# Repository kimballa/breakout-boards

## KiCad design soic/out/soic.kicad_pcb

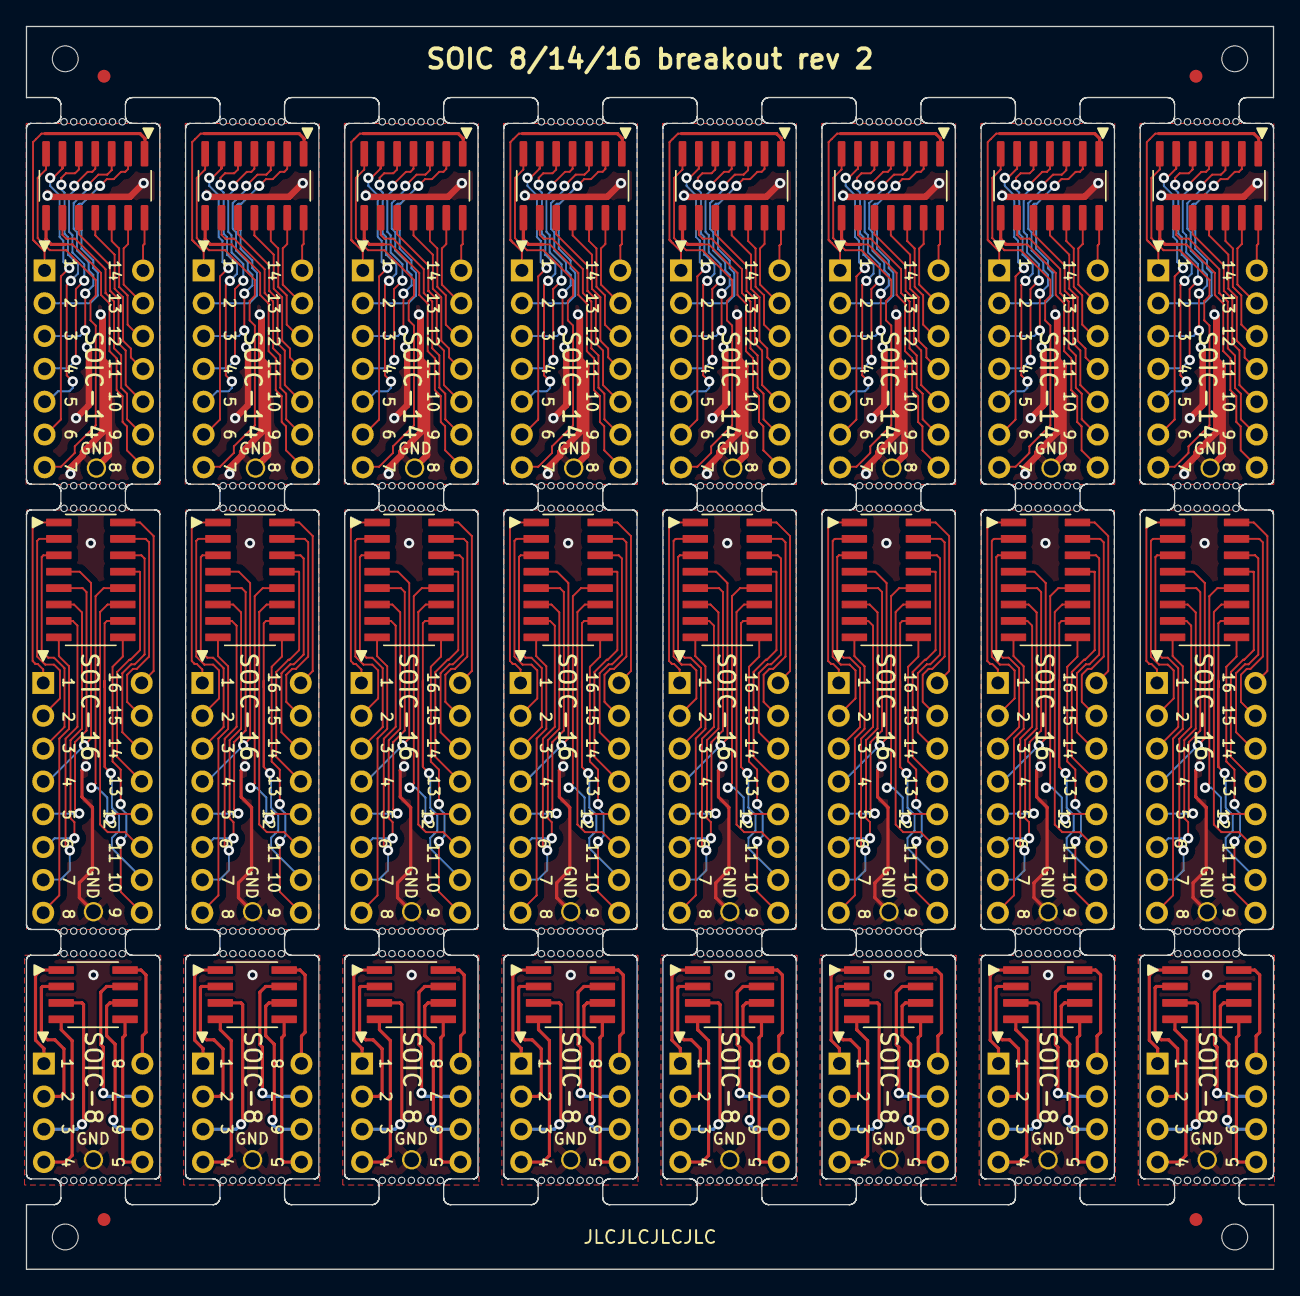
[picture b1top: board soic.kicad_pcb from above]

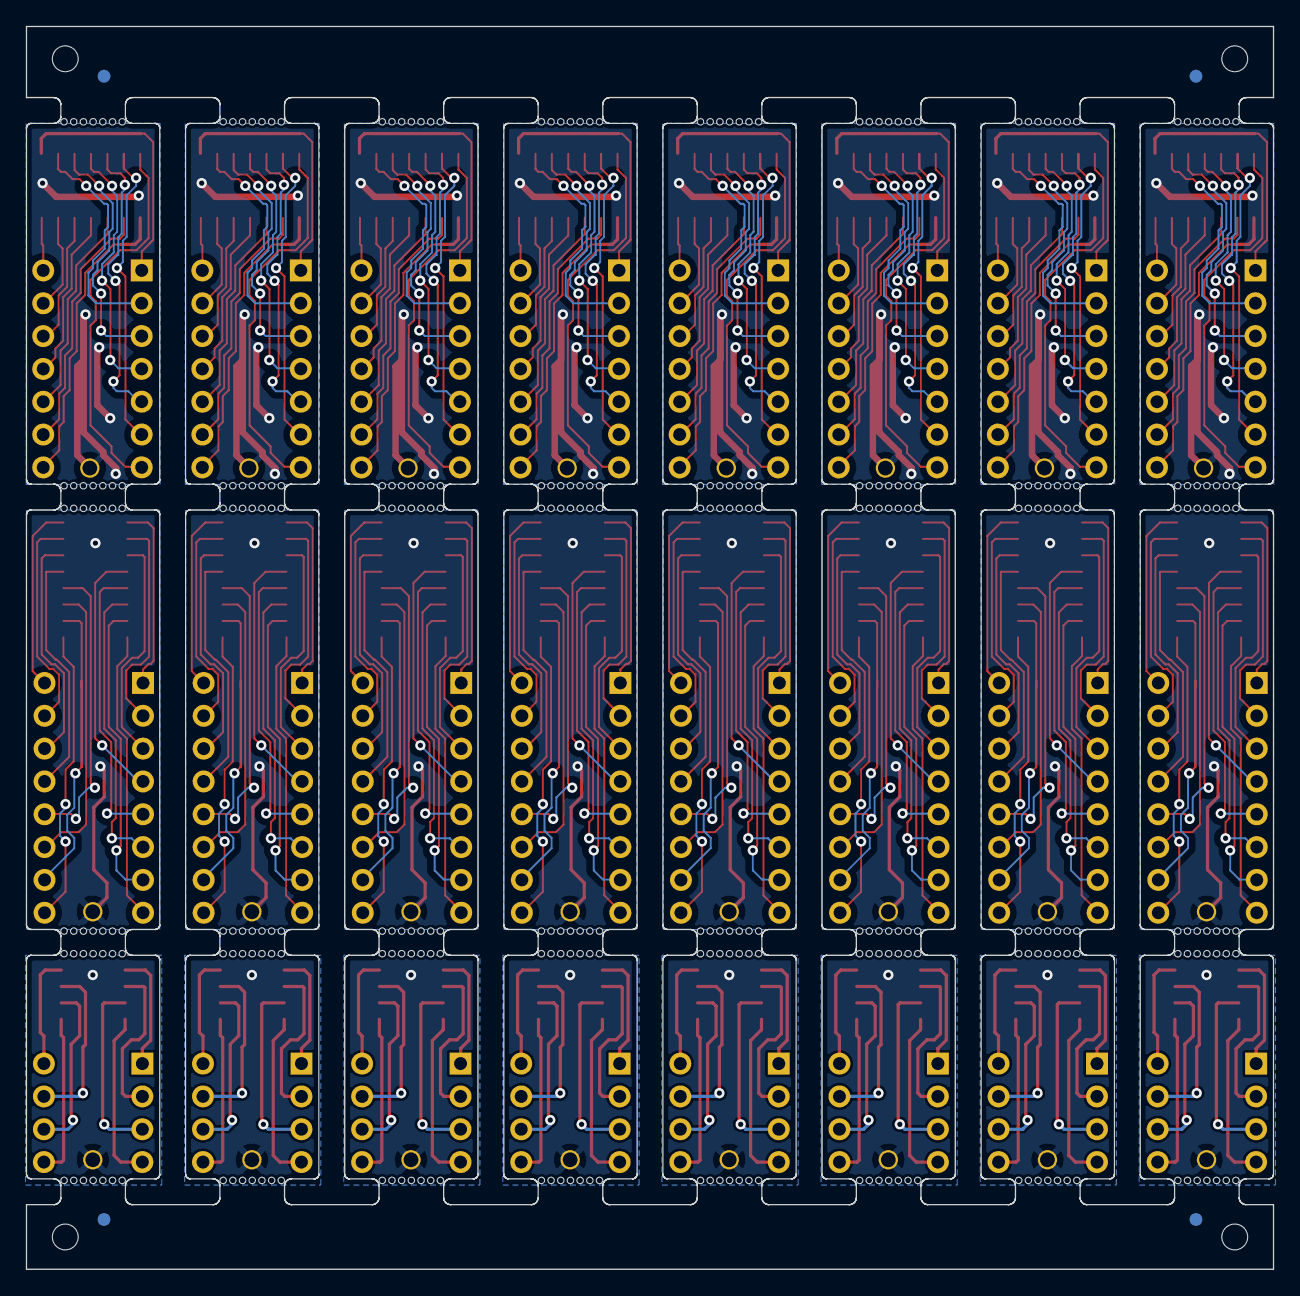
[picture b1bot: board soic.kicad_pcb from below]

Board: 2 copper layers, 96.5 x 96.2 mm, 444 parts (4 on the bottom side), 304 nets.

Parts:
J1, J1#2, J1#3, J1#4, J1#5, J1#6, J1#7, J1#8, J2, J2#2, J2#3, J2#4, J2#5, J2#6, J2#7, J2#8: Conn_01x07; PinHeader_1x07_P2.54mm_Vertical
J3, J3#2, J3#3, J3#4, J3#5, J3#6, J3#7, J3#8, J6, J6#2, J6#3, J6#4, J6#5, J6#6, J6#7, J6#8, J7, J7#2, J7#3, J7#4, J7#5, J7#6, J7#7, J7#8: Conn_01x01; TP_HeaderPin_P2.54mm_round
J4, J4#2, J4#3, J4#4, J4#5, J4#6, J4#7, J4#8, J5, J5#2, J5#3, J5#4, J5#5, J5#6, J5#7, J5#8: Conn_01x08; PinHeader_1x08_P2.54mm_Vertical
J8, J8#2, J8#3, J8#4, J8#5, J8#6, J8#7, J8#8, J9, J9#2, J9#3, J9#4, J9#5, J9#6, J9#7, J9#8: Conn_01x04; PinHeader_1x04_P2.54mm_Vertical
KiKit_FID_B_1, KiKit_FID_B_2, KiKit_FID_B_3, KiKit_FID_B_4: Fiducial
KiKit_FID_T_1, KiKit_FID_T_2, KiKit_FID_T_3, KiKit_FID_T_4: Fiducial
KiKit_MB_1_4, KiKit_MB_1_5, KiKit_MB_1_6, KiKit_MB_1_7, KiKit_MB_1_8, KiKit_MB_1_9, KiKit_MB_1_10, KiKit_MB_2_4, KiKit_MB_2_5, KiKit_MB_2_6, KiKit_MB_2_7, KiKit_MB_2_8, KiKit_MB_2_9, KiKit_MB_2_10, KiKit_MB_3_4, KiKit_MB_3_5, KiKit_MB_3_6, KiKit_MB_3_7, KiKit_MB_3_8, KiKit_MB_3_9, KiKit_MB_3_10, KiKit_MB_4_4, KiKit_MB_4_5, KiKit_MB_4_6, KiKit_MB_4_7, KiKit_MB_4_8, KiKit_MB_4_9, KiKit_MB_4_10, KiKit_MB_5_4, KiKit_MB_5_5, KiKit_MB_5_6, KiKit_MB_5_7, KiKit_MB_5_8, KiKit_MB_5_9, KiKit_MB_5_10, KiKit_MB_6_4, KiKit_MB_6_5, KiKit_MB_6_6, KiKit_MB_6_7, KiKit_MB_6_8, KiKit_MB_6_9, KiKit_MB_6_10, KiKit_MB_7_4, KiKit_MB_7_5, KiKit_MB_7_6, KiKit_MB_7_7, KiKit_MB_7_8, KiKit_MB_7_9, KiKit_MB_7_10, KiKit_MB_8_4, KiKit_MB_8_5, KiKit_MB_8_6, KiKit_MB_8_7, KiKit_MB_8_8, KiKit_MB_8_9, KiKit_MB_8_10, KiKit_MB_9_4, KiKit_MB_9_5, KiKit_MB_9_6, KiKit_MB_9_7, KiKit_MB_9_8, KiKit_MB_9_9, KiKit_MB_9_10, KiKit_MB_10_4, KiKit_MB_10_5, KiKit_MB_10_6, KiKit_MB_10_7, KiKit_MB_10_8, KiKit_MB_10_9, KiKit_MB_10_10, KiKit_MB_11_4, KiKit_MB_11_5, KiKit_MB_11_6, KiKit_MB_11_7, KiKit_MB_11_8, KiKit_MB_11_9, KiKit_MB_11_10, KiKit_MB_12_4, KiKit_MB_12_5, KiKit_MB_12_6, KiKit_MB_12_7, KiKit_MB_12_8, KiKit_MB_12_9, KiKit_MB_12_10, KiKit_MB_13_4, KiKit_MB_13_5, KiKit_MB_13_6, KiKit_MB_13_7, KiKit_MB_13_8, KiKit_MB_13_9, KiKit_MB_13_10, KiKit_MB_14_4, KiKit_MB_14_5, KiKit_MB_14_6, KiKit_MB_14_7, KiKit_MB_14_8, KiKit_MB_14_9, KiKit_MB_14_10, KiKit_MB_15_4, KiKit_MB_15_5, KiKit_MB_15_6, KiKit_MB_15_7, KiKit_MB_15_8, KiKit_MB_15_9, KiKit_MB_15_10, KiKit_MB_16_4, KiKit_MB_16_5, KiKit_MB_16_6, KiKit_MB_16_7, KiKit_MB_16_8, KiKit_MB_16_9, KiKit_MB_16_10, KiKit_MB_17_4, KiKit_MB_17_5, KiKit_MB_17_6, KiKit_MB_17_7, KiKit_MB_17_8, KiKit_MB_17_9, KiKit_MB_17_10, KiKit_MB_18_4, KiKit_MB_18_5, KiKit_MB_18_6, KiKit_MB_18_7, KiKit_MB_18_8, KiKit_MB_18_9, KiKit_MB_18_10, KiKit_MB_19_4, KiKit_MB_19_5, KiKit_MB_19_6, KiKit_MB_19_7, KiKit_MB_19_8, KiKit_MB_19_9, KiKit_MB_19_10, KiKit_MB_20_4, KiKit_MB_20_5, KiKit_MB_20_6, KiKit_MB_20_7, KiKit_MB_20_8, KiKit_MB_20_9, KiKit_MB_20_10, KiKit_MB_21_4, KiKit_MB_21_5, KiKit_MB_21_6, KiKit_MB_21_7, KiKit_MB_21_8, KiKit_MB_21_9, KiKit_MB_21_10, KiKit_MB_22_4, KiKit_MB_22_5, KiKit_MB_22_6, KiKit_MB_22_7, KiKit_MB_22_8, KiKit_MB_22_9, KiKit_MB_22_10, KiKit_MB_23_4, KiKit_MB_23_5, KiKit_MB_23_6, KiKit_MB_23_7, KiKit_MB_23_8, KiKit_MB_23_9, KiKit_MB_23_10, KiKit_MB_24_4, KiKit_MB_24_5, KiKit_MB_24_6, KiKit_MB_24_7, KiKit_MB_24_8, KiKit_MB_24_9, KiKit_MB_24_10, KiKit_MB_25_4, KiKit_MB_25_5, KiKit_MB_25_6, KiKit_MB_25_7, KiKit_MB_25_8, KiKit_MB_25_9, KiKit_MB_25_10, KiKit_MB_26_4, KiKit_MB_26_5, KiKit_MB_26_6, KiKit_MB_26_7, KiKit_MB_26_8, KiKit_MB_26_9, KiKit_MB_26_10, KiKit_MB_27_4, KiKit_MB_27_5, KiKit_MB_27_6, KiKit_MB_27_7, KiKit_MB_27_8, KiKit_MB_27_9, KiKit_MB_27_10, KiKit_MB_28_4, KiKit_MB_28_5, KiKit_MB_28_6, KiKit_MB_28_7, KiKit_MB_28_8, KiKit_MB_28_9, KiKit_MB_28_10, KiKit_MB_29_4, KiKit_MB_29_5, KiKit_MB_29_6, KiKit_MB_29_7, KiKit_MB_29_8, KiKit_MB_29_9, KiKit_MB_29_10, KiKit_MB_30_4, KiKit_MB_30_5, KiKit_MB_30_6, KiKit_MB_30_7, KiKit_MB_30_8, KiKit_MB_30_9, KiKit_MB_30_10, KiKit_MB_31_4, KiKit_MB_31_5, KiKit_MB_31_6, KiKit_MB_31_7, KiKit_MB_31_8, KiKit_MB_31_9, KiKit_MB_31_10, KiKit_MB_32_4, KiKit_MB_32_5, KiKit_MB_32_6, KiKit_MB_32_7, KiKit_MB_32_8, KiKit_MB_32_9, KiKit_MB_32_10, KiKit_MB_33_4, KiKit_MB_33_5, KiKit_MB_33_6, KiKit_MB_33_7, KiKit_MB_33_8, KiKit_MB_33_9, KiKit_MB_33_10, KiKit_MB_34_4, KiKit_MB_34_5, KiKit_MB_34_6, KiKit_MB_34_7, KiKit_MB_34_8, KiKit_MB_34_9, KiKit_MB_34_10, KiKit_MB_35_4, KiKit_MB_35_5, KiKit_MB_35_6, KiKit_MB_35_7, KiKit_MB_35_8, KiKit_MB_35_9, KiKit_MB_35_10, KiKit_MB_36_4, KiKit_MB_36_5, KiKit_MB_36_6, KiKit_MB_36_7, KiKit_MB_36_8, KiKit_MB_36_9, KiKit_MB_36_10, KiKit_MB_37_4, KiKit_MB_37_5, KiKit_MB_37_6, KiKit_MB_37_7, KiKit_MB_37_8, KiKit_MB_37_9, KiKit_MB_37_10, KiKit_MB_38_4, KiKit_MB_38_5, KiKit_MB_38_6, KiKit_MB_38_7, KiKit_MB_38_8, KiKit_MB_38_9, KiKit_MB_38_10, KiKit_MB_39_4, KiKit_MB_39_5, KiKit_MB_39_6, KiKit_MB_39_7, KiKit_MB_39_8, KiKit_MB_39_9, KiKit_MB_39_10, KiKit_MB_40_4, KiKit_MB_40_5, KiKit_MB_40_6, KiKit_MB_40_7, KiKit_MB_40_8, KiKit_MB_40_9, KiKit_MB_40_10, KiKit_MB_41_4, KiKit_MB_41_5, KiKit_MB_41_6, KiKit_MB_41_7, KiKit_MB_41_8, KiKit_MB_41_9, KiKit_MB_41_10, KiKit_MB_42_4, KiKit_MB_42_5, KiKit_MB_42_6, KiKit_MB_42_7, KiKit_MB_42_8, KiKit_MB_42_9, KiKit_MB_42_10, KiKit_MB_43_4, KiKit_MB_43_5, KiKit_MB_43_6, KiKit_MB_43_7, KiKit_MB_43_8, KiKit_MB_43_9, KiKit_MB_43_10, KiKit_MB_44_4, KiKit_MB_44_5, KiKit_MB_44_6, KiKit_MB_44_7, KiKit_MB_44_8, KiKit_MB_44_9, KiKit_MB_44_10, KiKit_MB_45_4, KiKit_MB_45_5, KiKit_MB_45_6, KiKit_MB_45_7, KiKit_MB_45_8, KiKit_MB_45_9, KiKit_MB_45_10, KiKit_MB_46_4, KiKit_MB_46_5, KiKit_MB_46_6, KiKit_MB_46_7, KiKit_MB_46_8, KiKit_MB_46_9, KiKit_MB_46_10, KiKit_MB_47_4, KiKit_MB_47_5, KiKit_MB_47_6, KiKit_MB_47_7, KiKit_MB_47_8, KiKit_MB_47_9, KiKit_MB_47_10, KiKit_MB_48_4, KiKit_MB_48_5, KiKit_MB_48_6, KiKit_MB_48_7, KiKit_MB_48_8, KiKit_MB_48_9, KiKit_MB_48_10: NPTH
KiKit_TO_1, KiKit_TO_2, KiKit_TO_3, KiKit_TO_4: NPTH
U1, U1#2, U1#3, U1#4, U1#5, U1#6, U1#7, U1#8: TL074; TI_SOIC_D_R-PDSO-G14
U2, U2#2, U2#3, U2#4, U2#5, U2#6, U2#7, U2#8: LM13700; TI_SOIC_D_R-PDSO-16
U3, U3#2, U3#3, U3#4, U3#5, U3#6, U3#7, U3#8: TL072; TI_SOIC_D_R-PDSO-8

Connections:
Board_0-Net-(J1-Pin_1): J1#4.1, U1#5.1
Board_0-Net-(J1-Pin_2): J1#4.2, U1#5.2 (-)
Board_0-Net-(J1-Pin_3): J1#4.3, U1#5.3 (+)
Board_0-Net-(J1-Pin_4): J1#4.4, U1#5.4 (V+)
Board_0-Net-(J1-Pin_5): J1#4.5, U1#5.5 (+)
Board_0-Net-(J1-Pin_6): J1#4.6, U1#5.6 (-)
Board_0-Net-(J1-Pin_7): J1#4.7, U1#5.7
Board_0-Net-(J2-Pin_1): J2#4.1, U1#5.8
Board_0-Net-(J2-Pin_2): J2#4.2, U1#5.9 (-)
Board_0-Net-(J2-Pin_3): J2#4.3, U1#5.10 (+)
Board_0-Net-(J2-Pin_4): J2#4.4, U1#5.11 (V-)
Board_0-Net-(J2-Pin_5): J2#4.5, U1#5.12 (+)
Board_0-Net-(J2-Pin_6): J2#4.6, U1#5.13 (-)
Board_0-Net-(J2-Pin_7): J2#4.7, U1#5.14
Board_1-Net-(J4-Pin_1): J4#8.1, U2#2.1
Board_1-Net-(J4-Pin_2): J4#8.2, U2#2.2 (DIODE_BIAS)
Board_1-Net-(J4-Pin_3): J4#8.3, U2#2.3 (+)
Board_1-Net-(J4-Pin_4): J4#8.4, U2#2.4 (-)
Board_1-Net-(J4-Pin_5): J4#8.5, U2#2.5
Board_1-Net-(J4-Pin_6): J4#8.6, U2#2.6 (V-)
Board_1-Net-(J4-Pin_7): J4#8.7, U2#2.7
Board_1-Net-(J4-Pin_8): J4#8.8, U2#2.8
Board_1-Net-(J5-Pin_1): J5#2.1, U2#2.9
Board_1-Net-(J5-Pin_2): J5#2.2, U2#2.10
Board_1-Net-(J5-Pin_3): J5#2.3, U2#2.11 (V+)
Board_1-Net-(J5-Pin_4): J5#2.4, U2#2.12
Board_1-Net-(J5-Pin_5): J5#2.5, U2#2.13 (-)
Board_1-Net-(J5-Pin_6): J5#2.6, U2#2.14 (+)
Board_1-Net-(J5-Pin_7): J5#2.7, U2#2.15 (DIODE_BIAS)
Board_1-Net-(J5-Pin_8): J5#2.8, U2#2.16
Board_2-Net-(J8-Pin_1): J8#3.1, U3#8.8 (V+)
Board_2-Net-(J8-Pin_2): J8#3.2, U3#8.7
Board_2-Net-(J8-Pin_3): J8#3.3, U3#8.6 (-)
Board_2-Net-(J8-Pin_4): J8#3.4, U3#8.5 (+)
Board_2-Net-(J9-Pin_1): J9#4.1, U3#8.1
Board_2-Net-(J9-Pin_2): J9#4.2, U3#8.2 (-)
Board_2-Net-(J9-Pin_3): J9#4.3, U3#8.3 (+)
Board_2-Net-(J9-Pin_4): J9#4.4, U3#8.4 (V-)
Board_3-Net-(J1-Pin_1): J1#5.1, U1#4.1
Board_3-Net-(J1-Pin_2): J1#5.2, U1#4.2 (-)
Board_3-Net-(J1-Pin_3): J1#5.3, U1#4.3 (+)
Board_3-Net-(J1-Pin_4): J1#5.4, U1#4.4 (V+)
Board_3-Net-(J1-Pin_5): J1#5.5, U1#4.5 (+)
Board_3-Net-(J1-Pin_6): J1#5.6, U1#4.6 (-)
Board_3-Net-(J1-Pin_7): J1#5.7, U1#4.7
Board_3-Net-(J2-Pin_1): J2#7.1, U1#4.8
Board_3-Net-(J2-Pin_2): J2#7.2, U1#4.9 (-)
Board_3-Net-(J2-Pin_3): J2#7.3, U1#4.10 (+)
Board_3-Net-(J2-Pin_4): J2#7.4, U1#4.11 (V-)
Board_3-Net-(J2-Pin_5): J2#7.5, U1#4.12 (+)
Board_3-Net-(J2-Pin_6): J2#7.6, U1#4.13 (-)
Board_3-Net-(J2-Pin_7): J2#7.7, U1#4.14
Board_4-Net-(J4-Pin_1): J4#2.1, U2.1
Board_4-Net-(J4-Pin_2): J4#2.2, U2.2 (DIODE_BIAS)
Board_4-Net-(J4-Pin_3): J4#2.3, U2.3 (+)
Board_4-Net-(J4-Pin_4): J4#2.4, U2.4 (-)
Board_4-Net-(J4-Pin_5): J4#2.5, U2.5
Board_4-Net-(J4-Pin_6): J4#2.6, U2.6 (V-)
Board_4-Net-(J4-Pin_7): J4#2.7, U2.7
Board_4-Net-(J4-Pin_8): J4#2.8, U2.8
Board_4-Net-(J5-Pin_1): J5#6.1, U2.9
Board_4-Net-(J5-Pin_2): J5#6.2, U2.10
Board_4-Net-(J5-Pin_3): J5#6.3, U2.11 (V+)
Board_4-Net-(J5-Pin_4): J5#6.4, U2.12
Board_4-Net-(J5-Pin_5): J5#6.5, U2.13 (-)
Board_4-Net-(J5-Pin_6): J5#6.6, U2.14 (+)
Board_4-Net-(J5-Pin_7): J5#6.7, U2.15 (DIODE_BIAS)
Board_4-Net-(J5-Pin_8): J5#6.8, U2.16
Board_5-Net-(J8-Pin_1): J8#5.1, U3#4.8 (V+)
Board_5-Net-(J8-Pin_2): J8#5.2, U3#4.7
Board_5-Net-(J8-Pin_3): J8#5.3, U3#4.6 (-)
Board_5-Net-(J8-Pin_4): J8#5.4, U3#4.5 (+)
Board_5-Net-(J9-Pin_1): J9.1, U3#4.1
Board_5-Net-(J9-Pin_2): J9.2, U3#4.2 (-)
Board_5-Net-(J9-Pin_3): J9.3, U3#4.3 (+)
Board_5-Net-(J9-Pin_4): J9.4, U3#4.4 (V-)
Board_6-Net-(J1-Pin_1): J1#3.1, U1#6.1
Board_6-Net-(J1-Pin_2): J1#3.2, U1#6.2 (-)
Board_6-Net-(J1-Pin_3): J1#3.3, U1#6.3 (+)
Board_6-Net-(J1-Pin_4): J1#3.4, U1#6.4 (V+)
Board_6-Net-(J1-Pin_5): J1#3.5, U1#6.5 (+)
Board_6-Net-(J1-Pin_6): J1#3.6, U1#6.6 (-)
Board_6-Net-(J1-Pin_7): J1#3.7, U1#6.7
Board_6-Net-(J2-Pin_1): J2#8.1, U1#6.8
Board_6-Net-(J2-Pin_2): J2#8.2, U1#6.9 (-)
Board_6-Net-(J2-Pin_3): J2#8.3, U1#6.10 (+)
Board_6-Net-(J2-Pin_4): J2#8.4, U1#6.11 (V-)
Board_6-Net-(J2-Pin_5): J2#8.5, U1#6.12 (+)
Board_6-Net-(J2-Pin_6): J2#8.6, U1#6.13 (-)
Board_6-Net-(J2-Pin_7): J2#8.7, U1#6.14
Board_7-Net-(J4-Pin_1): J4#6.1, U2#5.1
Board_7-Net-(J4-Pin_2): J4#6.2, U2#5.2 (DIODE_BIAS)
Board_7-Net-(J4-Pin_3): J4#6.3, U2#5.3 (+)
Board_7-Net-(J4-Pin_4): J4#6.4, U2#5.4 (-)
Board_7-Net-(J4-Pin_5): J4#6.5, U2#5.5
Board_7-Net-(J4-Pin_6): J4#6.6, U2#5.6 (V-)
Board_7-Net-(J4-Pin_7): J4#6.7, U2#5.7
Board_7-Net-(J4-Pin_8): J4#6.8, U2#5.8
Board_7-Net-(J5-Pin_1): J5#7.1, U2#5.9
Board_7-Net-(J5-Pin_2): J5#7.2, U2#5.10
Board_7-Net-(J5-Pin_3): J5#7.3, U2#5.11 (V+)
Board_7-Net-(J5-Pin_4): J5#7.4, U2#5.12
Board_7-Net-(J5-Pin_5): J5#7.5, U2#5.13 (-)
Board_7-Net-(J5-Pin_6): J5#7.6, U2#5.14 (+)
Board_7-Net-(J5-Pin_7): J5#7.7, U2#5.15 (DIODE_BIAS)
Board_7-Net-(J5-Pin_8): J5#7.8, U2#5.16
Board_8-Net-(J8-Pin_1): J8#8.1, U3#7.8 (V+)
Board_8-Net-(J8-Pin_2): J8#8.2, U3#7.7
Board_8-Net-(J8-Pin_3): J8#8.3, U3#7.6 (-)
Board_8-Net-(J8-Pin_4): J8#8.4, U3#7.5 (+)
Board_8-Net-(J9-Pin_1): J9#2.1, U3#7.1
Board_8-Net-(J9-Pin_2): J9#2.2, U3#7.2 (-)
Board_8-Net-(J9-Pin_3): J9#2.3, U3#7.3 (+)
Board_8-Net-(J9-Pin_4): J9#2.4, U3#7.4 (V-)
Board_9-Net-(J1-Pin_1): J1.1, U1#7.1
Board_9-Net-(J1-Pin_2): J1.2, U1#7.2 (-)
Board_9-Net-(J1-Pin_3): J1.3, U1#7.3 (+)
Board_9-Net-(J1-Pin_4): J1.4, U1#7.4 (V+)
Board_9-Net-(J1-Pin_5): J1.5, U1#7.5 (+)
Board_9-Net-(J1-Pin_6): J1.6, U1#7.6 (-)
Board_9-Net-(J1-Pin_7): J1.7, U1#7.7
Board_9-Net-(J2-Pin_1): J2#2.1, U1#7.8
Board_9-Net-(J2-Pin_2): J2#2.2, U1#7.9 (-)
Board_9-Net-(J2-Pin_3): J2#2.3, U1#7.10 (+)
Board_9-Net-(J2-Pin_4): J2#2.4, U1#7.11 (V-)
Board_9-Net-(J2-Pin_5): J2#2.5, U1#7.12 (+)
Board_9-Net-(J2-Pin_6): J2#2.6, U1#7.13 (-)
Board_9-Net-(J2-Pin_7): J2#2.7, U1#7.14
Board_10-Net-(J4-Pin_1): J4#3.1, U2#8.1
Board_10-Net-(J4-Pin_2): J4#3.2, U2#8.2 (DIODE_BIAS)
Board_10-Net-(J4-Pin_3): J4#3.3, U2#8.3 (+)
Board_10-Net-(J4-Pin_4): J4#3.4, U2#8.4 (-)
Board_10-Net-(J4-Pin_5): J4#3.5, U2#8.5
Board_10-Net-(J4-Pin_6): J4#3.6, U2#8.6 (V-)
Board_10-Net-(J4-Pin_7): J4#3.7, U2#8.7
Board_10-Net-(J4-Pin_8): J4#3.8, U2#8.8
Board_10-Net-(J5-Pin_1): J5#4.1, U2#8.9
Board_10-Net-(J5-Pin_2): J5#4.2, U2#8.10
Board_10-Net-(J5-Pin_3): J5#4.3, U2#8.11 (V+)
Board_10-Net-(J5-Pin_4): J5#4.4, U2#8.12
Board_10-Net-(J5-Pin_5): J5#4.5, U2#8.13 (-)
Board_10-Net-(J5-Pin_6): J5#4.6, U2#8.14 (+)
Board_10-Net-(J5-Pin_7): J5#4.7, U2#8.15 (DIODE_BIAS)
Board_10-Net-(J5-Pin_8): J5#4.8, U2#8.16
Board_11-Net-(J8-Pin_1): J8#6.1, U3#3.8 (V+)
Board_11-Net-(J8-Pin_2): J8#6.2, U3#3.7
Board_11-Net-(J8-Pin_3): J8#6.3, U3#3.6 (-)
Board_11-Net-(J8-Pin_4): J8#6.4, U3#3.5 (+)
Board_11-Net-(J9-Pin_1): J9#3.1, U3#3.1
Board_11-Net-(J9-Pin_2): J9#3.2, U3#3.2 (-)
Board_11-Net-(J9-Pin_3): J9#3.3, U3#3.3 (+)
Board_11-Net-(J9-Pin_4): J9#3.4, U3#3.4 (V-)
Board_12-Net-(J1-Pin_1): J1#8.1, U1.1
Board_12-Net-(J1-Pin_2): J1#8.2, U1.2 (-)
Board_12-Net-(J1-Pin_3): J1#8.3, U1.3 (+)
Board_12-Net-(J1-Pin_4): J1#8.4, U1.4 (V+)
Board_12-Net-(J1-Pin_5): J1#8.5, U1.5 (+)
Board_12-Net-(J1-Pin_6): J1#8.6, U1.6 (-)
Board_12-Net-(J1-Pin_7): J1#8.7, U1.7
Board_12-Net-(J2-Pin_1): J2#6.1, U1.8
Board_12-Net-(J2-Pin_2): J2#6.2, U1.9 (-)
Board_12-Net-(J2-Pin_3): J2#6.3, U1.10 (+)
Board_12-Net-(J2-Pin_4): J2#6.4, U1.11 (V-)
Board_12-Net-(J2-Pin_5): J2#6.5, U1.12 (+)
Board_12-Net-(J2-Pin_6): J2#6.6, U1.13 (-)
Board_12-Net-(J2-Pin_7): J2#6.7, U1.14
Board_13-Net-(J4-Pin_1): J4#7.1, U2#4.1
Board_13-Net-(J4-Pin_2): J4#7.2, U2#4.2 (DIODE_BIAS)
Board_13-Net-(J4-Pin_3): J4#7.3, U2#4.3 (+)
Board_13-Net-(J4-Pin_4): J4#7.4, U2#4.4 (-)
Board_13-Net-(J4-Pin_5): J4#7.5, U2#4.5
Board_13-Net-(J4-Pin_6): J4#7.6, U2#4.6 (V-)
Board_13-Net-(J4-Pin_7): J4#7.7, U2#4.7
Board_13-Net-(J4-Pin_8): J4#7.8, U2#4.8
Board_13-Net-(J5-Pin_1): J5.1, U2#4.9
Board_13-Net-(J5-Pin_2): J5.2, U2#4.10
Board_13-Net-(J5-Pin_3): J5.3, U2#4.11 (V+)
Board_13-Net-(J5-Pin_4): J5.4, U2#4.12
Board_13-Net-(J5-Pin_5): J5.5, U2#4.13 (-)
Board_13-Net-(J5-Pin_6): J5.6, U2#4.14 (+)
Board_13-Net-(J5-Pin_7): J5.7, U2#4.15 (DIODE_BIAS)
Board_13-Net-(J5-Pin_8): J5.8, U2#4.16
Board_14-Net-(J8-Pin_1): J8#4.1, U3#5.8 (V+)
Board_14-Net-(J8-Pin_2): J8#4.2, U3#5.7
Board_14-Net-(J8-Pin_3): J8#4.3, U3#5.6 (-)
Board_14-Net-(J8-Pin_4): J8#4.4, U3#5.5 (+)
Board_14-Net-(J9-Pin_1): J9#8.1, U3#5.1
Board_14-Net-(J9-Pin_2): J9#8.2, U3#5.2 (-)
Board_14-Net-(J9-Pin_3): J9#8.3, U3#5.3 (+)
Board_14-Net-(J9-Pin_4): J9#8.4, U3#5.4 (V-)
Board_15-Net-(J1-Pin_1): J1#6.1, U1#3.1
Board_15-Net-(J1-Pin_2): J1#6.2, U1#3.2 (-)
Board_15-Net-(J1-Pin_3): J1#6.3, U1#3.3 (+)
Board_15-Net-(J1-Pin_4): J1#6.4, U1#3.4 (V+)
Board_15-Net-(J1-Pin_5): J1#6.5, U1#3.5 (+)
Board_15-Net-(J1-Pin_6): J1#6.6, U1#3.6 (-)
Board_15-Net-(J1-Pin_7): J1#6.7, U1#3.7
Board_15-Net-(J2-Pin_1): J2.1, U1#3.8
Board_15-Net-(J2-Pin_2): J2.2, U1#3.9 (-)
Board_15-Net-(J2-Pin_3): J2.3, U1#3.10 (+)
Board_15-Net-(J2-Pin_4): J2.4, U1#3.11 (V-)
Board_15-Net-(J2-Pin_5): J2.5, U1#3.12 (+)
Board_15-Net-(J2-Pin_6): J2.6, U1#3.13 (-)
Board_15-Net-(J2-Pin_7): J2.7, U1#3.14
Board_16-Net-(J4-Pin_1): J4#5.1, U2#6.1
Board_16-Net-(J4-Pin_2): J4#5.2, U2#6.2 (DIODE_BIAS)
Board_16-Net-(J4-Pin_3): J4#5.3, U2#6.3 (+)
Board_16-Net-(J4-Pin_4): J4#5.4, U2#6.4 (-)
Board_16-Net-(J4-Pin_5): J4#5.5, U2#6.5
Board_16-Net-(J4-Pin_6): J4#5.6, U2#6.6 (V-)
Board_16-Net-(J4-Pin_7): J4#5.7, U2#6.7
Board_16-Net-(J4-Pin_8): J4#5.8, U2#6.8
Board_16-Net-(J5-Pin_1): J5#8.1, U2#6.9
Board_16-Net-(J5-Pin_2): J5#8.2, U2#6.10
Board_16-Net-(J5-Pin_3): J5#8.3, U2#6.11 (V+)
Board_16-Net-(J5-Pin_4): J5#8.4, U2#6.12
Board_16-Net-(J5-Pin_5): J5#8.5, U2#6.13 (-)
Board_16-Net-(J5-Pin_6): J5#8.6, U2#6.14 (+)
Board_16-Net-(J5-Pin_7): J5#8.7, U2#6.15 (DIODE_BIAS)
Board_16-Net-(J5-Pin_8): J5#8.8, U2#6.16
Board_17-Net-(J8-Pin_1): J8.1, U3#6.8 (V+)
Board_17-Net-(J8-Pin_2): J8.2, U3#6.7
Board_17-Net-(J8-Pin_3): J8.3, U3#6.6 (-)
Board_17-Net-(J8-Pin_4): J8.4, U3#6.5 (+)
Board_17-Net-(J9-Pin_1): J9#7.1, U3#6.1
Board_17-Net-(J9-Pin_2): J9#7.2, U3#6.2 (-)
Board_17-Net-(J9-Pin_3): J9#7.3, U3#6.3 (+)
Board_17-Net-(J9-Pin_4): J9#7.4, U3#6.4 (V-)
Board_18-Net-(J1-Pin_1): J1#2.1, U1#2.1
Board_18-Net-(J1-Pin_2): J1#2.2, U1#2.2 (-)
Board_18-Net-(J1-Pin_3): J1#2.3, U1#2.3 (+)
Board_18-Net-(J1-Pin_4): J1#2.4, U1#2.4 (V+)
Board_18-Net-(J1-Pin_5): J1#2.5, U1#2.5 (+)
Board_18-Net-(J1-Pin_6): J1#2.6, U1#2.6 (-)
Board_18-Net-(J1-Pin_7): J1#2.7, U1#2.7
Board_18-Net-(J2-Pin_1): J2#5.1, U1#2.8
Board_18-Net-(J2-Pin_2): J2#5.2, U1#2.9 (-)
Board_18-Net-(J2-Pin_3): J2#5.3, U1#2.10 (+)
Board_18-Net-(J2-Pin_4): J2#5.4, U1#2.11 (V-)
Board_18-Net-(J2-Pin_5): J2#5.5, U1#2.12 (+)
Board_18-Net-(J2-Pin_6): J2#5.6, U1#2.13 (-)
Board_18-Net-(J2-Pin_7): J2#5.7, U1#2.14
Board_19-Net-(J4-Pin_1): J4#4.1, U2#7.1
Board_19-Net-(J4-Pin_2): J4#4.2, U2#7.2 (DIODE_BIAS)
Board_19-Net-(J4-Pin_3): J4#4.3, U2#7.3 (+)
Board_19-Net-(J4-Pin_4): J4#4.4, U2#7.4 (-)
Board_19-Net-(J4-Pin_5): J4#4.5, U2#7.5
Board_19-Net-(J4-Pin_6): J4#4.6, U2#7.6 (V-)
Board_19-Net-(J4-Pin_7): J4#4.7, U2#7.7
Board_19-Net-(J4-Pin_8): J4#4.8, U2#7.8
Board_19-Net-(J5-Pin_1): J5#5.1, U2#7.9
Board_19-Net-(J5-Pin_2): J5#5.2, U2#7.10
Board_19-Net-(J5-Pin_3): J5#5.3, U2#7.11 (V+)
Board_19-Net-(J5-Pin_4): J5#5.4, U2#7.12
Board_19-Net-(J5-Pin_5): J5#5.5, U2#7.13 (-)
Board_19-Net-(J5-Pin_6): J5#5.6, U2#7.14 (+)
Board_19-Net-(J5-Pin_7): J5#5.7, U2#7.15 (DIODE_BIAS)
Board_19-Net-(J5-Pin_8): J5#5.8, U2#7.16
Board_20-Net-(J8-Pin_1): J8#2.1, U3#2.8 (V+)
Board_20-Net-(J8-Pin_2): J8#2.2, U3#2.7
Board_20-Net-(J8-Pin_3): J8#2.3, U3#2.6 (-)
Board_20-Net-(J8-Pin_4): J8#2.4, U3#2.5 (+)
Board_20-Net-(J9-Pin_1): J9#6.1, U3#2.1
Board_20-Net-(J9-Pin_2): J9#6.2, U3#2.2 (-)
Board_20-Net-(J9-Pin_3): J9#6.3, U3#2.3 (+)
Board_20-Net-(J9-Pin_4): J9#6.4, U3#2.4 (V-)
Board_21-Net-(J1-Pin_1): J1#7.1, U1#8.1
Board_21-Net-(J1-Pin_2): J1#7.2, U1#8.2 (-)
Board_21-Net-(J1-Pin_3): J1#7.3, U1#8.3 (+)
Board_21-Net-(J1-Pin_4): J1#7.4, U1#8.4 (V+)
Board_21-Net-(J1-Pin_5): J1#7.5, U1#8.5 (+)
Board_21-Net-(J1-Pin_6): J1#7.6, U1#8.6 (-)
Board_21-Net-(J1-Pin_7): J1#7.7, U1#8.7
Board_21-Net-(J2-Pin_1): J2#3.1, U1#8.8
Board_21-Net-(J2-Pin_2): J2#3.2, U1#8.9 (-)
Board_21-Net-(J2-Pin_3): J2#3.3, U1#8.10 (+)
Board_21-Net-(J2-Pin_4): J2#3.4, U1#8.11 (V-)
Board_21-Net-(J2-Pin_5): J2#3.5, U1#8.12 (+)
Board_21-Net-(J2-Pin_6): J2#3.6, U1#8.13 (-)
Board_21-Net-(J2-Pin_7): J2#3.7, U1#8.14
Board_22-Net-(J4-Pin_1): J4.1, U2#3.1
Board_22-Net-(J4-Pin_2): J4.2, U2#3.2 (DIODE_BIAS)
Board_22-Net-(J4-Pin_3): J4.3, U2#3.3 (+)
Board_22-Net-(J4-Pin_4): J4.4, U2#3.4 (-)
Board_22-Net-(J4-Pin_5): J4.5, U2#3.5
Board_22-Net-(J4-Pin_6): J4.6, U2#3.6 (V-)
Board_22-Net-(J4-Pin_7): J4.7, U2#3.7
Board_22-Net-(J4-Pin_8): J4.8, U2#3.8
Board_22-Net-(J5-Pin_1): J5#3.1, U2#3.9
Board_22-Net-(J5-Pin_2): J5#3.2, U2#3.10
Board_22-Net-(J5-Pin_3): J5#3.3, U2#3.11 (V+)
Board_22-Net-(J5-Pin_4): J5#3.4, U2#3.12
Board_22-Net-(J5-Pin_5): J5#3.5, U2#3.13 (-)
Board_22-Net-(J5-Pin_6): J5#3.6, U2#3.14 (+)
Board_22-Net-(J5-Pin_7): J5#3.7, U2#3.15 (DIODE_BIAS)
Board_22-Net-(J5-Pin_8): J5#3.8, U2#3.16
Board_23-Net-(J8-Pin_1): J8#7.1, U3.8 (V+)
Board_23-Net-(J8-Pin_2): J8#7.2, U3.7
Board_23-Net-(J8-Pin_3): J8#7.3, U3.6 (-)
Board_23-Net-(J8-Pin_4): J8#7.4, U3.5 (+)
Board_23-Net-(J9-Pin_1): J9#5.1, U3.1
Board_23-Net-(J9-Pin_2): J9#5.2, U3.2 (-)
Board_23-Net-(J9-Pin_3): J9#5.3, U3.3 (+)
Board_23-Net-(J9-Pin_4): J9#5.4, U3.4 (V-)
